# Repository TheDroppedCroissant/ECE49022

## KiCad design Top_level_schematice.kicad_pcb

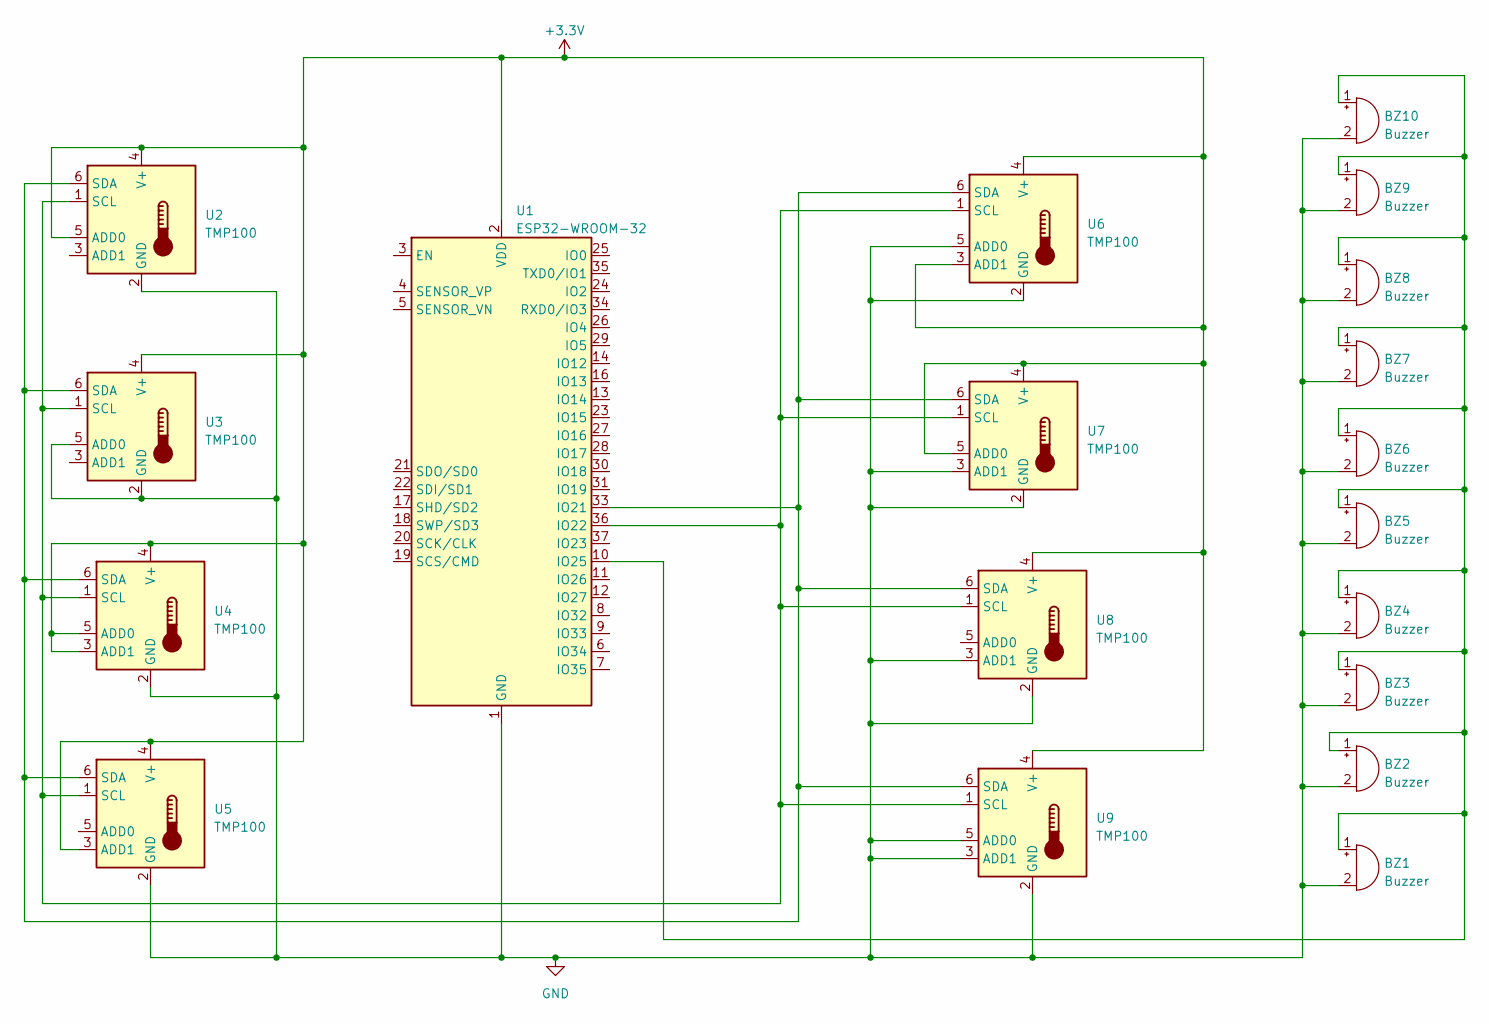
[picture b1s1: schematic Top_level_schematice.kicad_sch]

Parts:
BZ1, BZ2, BZ3, BZ4, BZ5, BZ6, BZ7, BZ8, BZ9, BZ10: Buzzer; Buzzer_12x9.5RM7.6
U1: ESP32-WROOM-32
U2, U3, U4, U5, U6, U7, U8, U9: TMP100; SOT-23-6

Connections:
+3.3V: U1.2 (VDD), U2.4 (V+), U2.5 (ADD0), U3.4 (V+), U4.3 (ADD1), U4.4 (V+), U4.5 (ADD0), U5.3 (ADD1), U5.4 (V+), U6.3 (ADD1), U6.4 (V+), U7.4 (V+), U7.5 (ADD0), U8.4 (V+), U9.4 (V+)
GND: BZ1.2 (+), BZ2.2 (+), BZ3.2 (+), BZ4.2 (+), BZ5.2 (+), BZ6.2 (+), BZ7.2 (+), BZ8.2 (+), BZ9.2 (+), BZ10.2 (+), U1.1 (GND), U1.15 (GND), U1.38 (GND), U1.39 (GND), U2.2 (GND), U3.2 (GND), U3.5 (ADD0), U4.2 (GND), U5.2 (GND), U6.2 (GND), U6.5 (ADD0), U7.2 (GND), U7.3 (ADD1), U8.2 (GND), U8.3 (ADD1), U9.2 (GND), U9.3 (ADD1), U9.5 (ADD0)
unnamed: BZ1.1 (-), BZ2.1 (-), BZ3.1 (-), BZ4.1 (-), BZ5.1 (-), BZ6.1 (-), BZ7.1 (-), BZ8.1 (-), BZ9.1 (-), BZ10.1 (-), U1.10 (IO25)
unnamed: U1.33 (IO21), U2.6 (SDA), U3.6 (SDA), U4.6 (SDA), U5.6 (SDA), U6.6 (SDA), U7.6 (SDA), U8.6 (SDA), U9.6 (SDA)
unnamed: U1.36 (IO22), U2.1 (SCL), U3.1 (SCL), U4.1 (SCL), U5.1 (SCL), U6.1 (SCL), U7.1 (SCL), U8.1 (SCL), U9.1 (SCL)

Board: 2 copper layers, 19 parts (0 on the bottom side), 5 nets, no tracks yet.

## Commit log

2024-02-13 Create Tmp_port
2024-03-07 Added schematic
    Added (outdated) schematic for the alarm subsystem.
